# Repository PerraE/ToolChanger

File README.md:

# ToolChanger
ToolChanger for Emco 120P. 

This tool changer will be used in a PathPilot (LinuxCNC) controller for a Emoc 120P lathe
Components for PathPilot is Mesa 7i92 and 7i76,

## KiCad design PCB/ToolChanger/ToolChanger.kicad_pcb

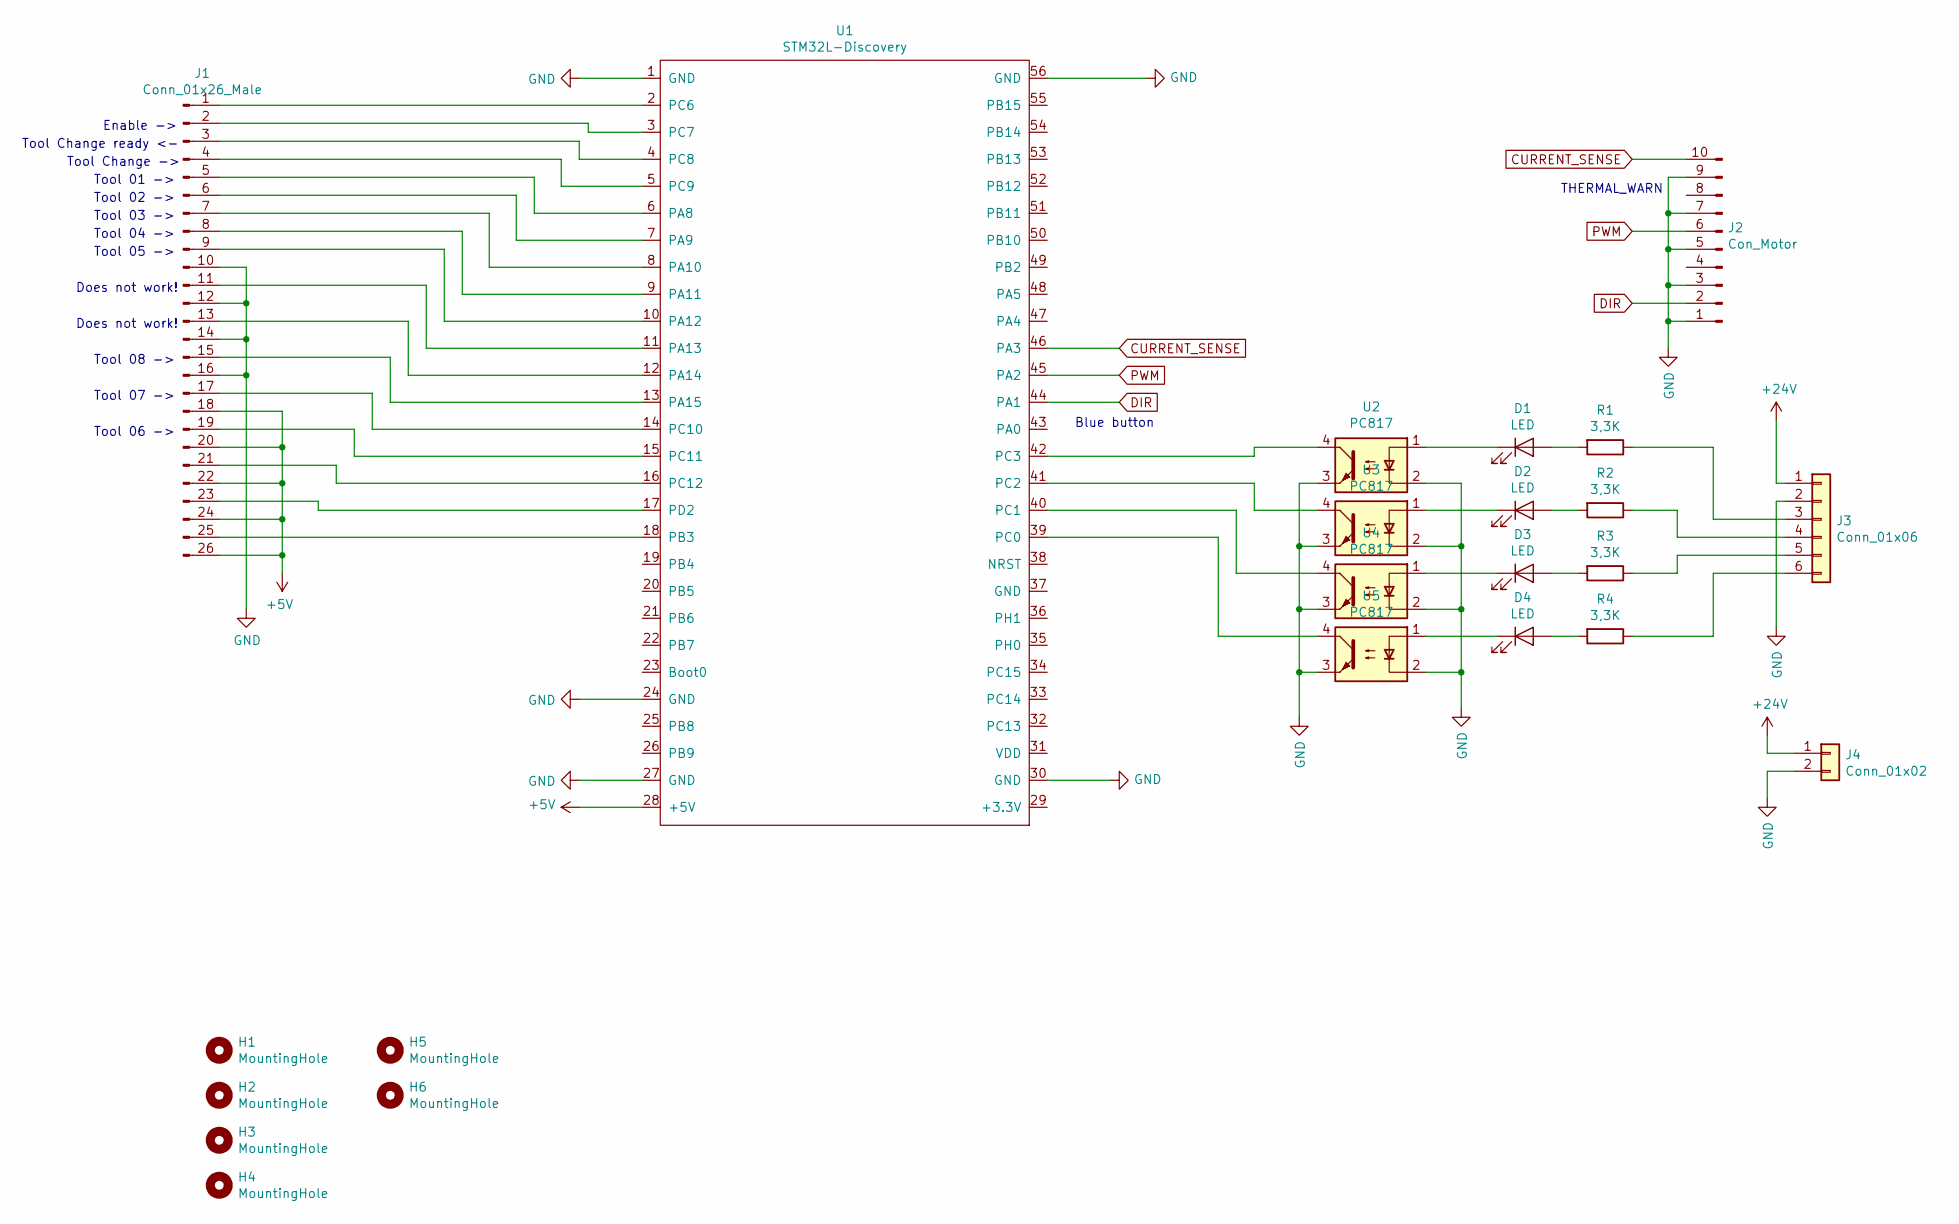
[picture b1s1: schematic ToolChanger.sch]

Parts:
D1, D2, D3, D4: LED; LED_D3.0mm
H1, H2, H3, H4, H5, H6: MountingHole; MountingHole_3.5mm
J1: Conn_01x26_Male; IDC-Header_2x13_P2.54mm_Vertical
J2: Con_Motor; IDC-Header_2x05_P2.54mm_Vertical
J3: Conn_01x06; PhoenixContact_MC_1,5_6-G-5.08_1x06_P5.08mm_Horizontal
J4: Conn_01x02; PhoenixContact_MC_1,5_2-G-5.08_1x02_P5.08mm_Horizontal
R1, R2, R3, R4: 3,3K; R_Axial_DIN0309_L9.0mm_D3.2mm_P12.70mm_Horizontal
U1: STM32L-Discovery
U2, U3, U4, U5: PC817; DIP-4_W7.62mm

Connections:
+5V: J1.18, J1.20, J1.22, J1.24, J1.26, U1.28 (+5V)
+24V: J3.1, J4.1
CURRENT_SENSE: J2.10, U1.46 (PA3)
DIR: J2.2, U1.44 (PA1)
GND: J1.10, J1.12, J1.14, J1.16, J2.1, J2.3, J2.5, J2.7, J2.9, J3.2, J4.2, U1.1 (GND), U1.24 (GND), U1.27 (GND), U1.30 (GND), U1.56 (GND), U2.2, U2.3, U3.2, U3.3, U4.2, U4.3, U5.2, U5.3
unnamed: D1.1 (K), U2.1
unnamed: D1.2 (A), R1.2
unnamed: D2.1 (K), U3.1
unnamed: D2.2 (A), R2.2
unnamed: D3.1 (K), U4.1
unnamed: D3.2 (A), R3.2
unnamed: D4.1 (K), U5.1
unnamed: D4.2 (A), R4.2
unnamed: J1.1, U1.2 (PC6)
unnamed: J1.2, U1.3 (PC7)
unnamed: J1.3, U1.4 (PC8)
unnamed: J1.4, U1.5 (PC9)
unnamed: J1.5, U1.6 (PA8)
unnamed: J1.6, U1.7 (PA9)
unnamed: J1.7, U1.8 (PA10)
unnamed: J1.8, U1.9 (PA11)
unnamed: J1.9, U1.10 (PA12)
unnamed: J1.11, U1.11 (PA13)
unnamed: J1.13, U1.12 (PA14)
unnamed: J1.15, U1.13 (PA15)
unnamed: J1.17, U1.14 (PC10)
unnamed: J1.19, U1.15 (PC11)
unnamed: J1.21, U1.16 (PC12)
unnamed: J1.23, U1.17 (PD2)
unnamed: J1.25, U1.18 (PB3)
unnamed: J3.3, R1.1
unnamed: J3.4, R2.1
unnamed: J3.5, R3.1
unnamed: J3.6, R4.1
unnamed: U1.39 (PC0), U5.4
unnamed: U1.40 (PC1), U4.4
unnamed: U1.41 (PC2), U3.4
unnamed: U1.42 (PC3), U2.4
PWM: J2.6, U1.45 (PA2)

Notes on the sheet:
Blue button
THERMAL_WARN
Enable ->
Tool Change ready <-
Tool Change ->
Tool 01 ->
Tool 02 ->
Tool 03 ->
Tool 04 ->
Tool 05 ->
Tool 06 ->
Tool 07 ->
Tool 08 ->
Does not work!

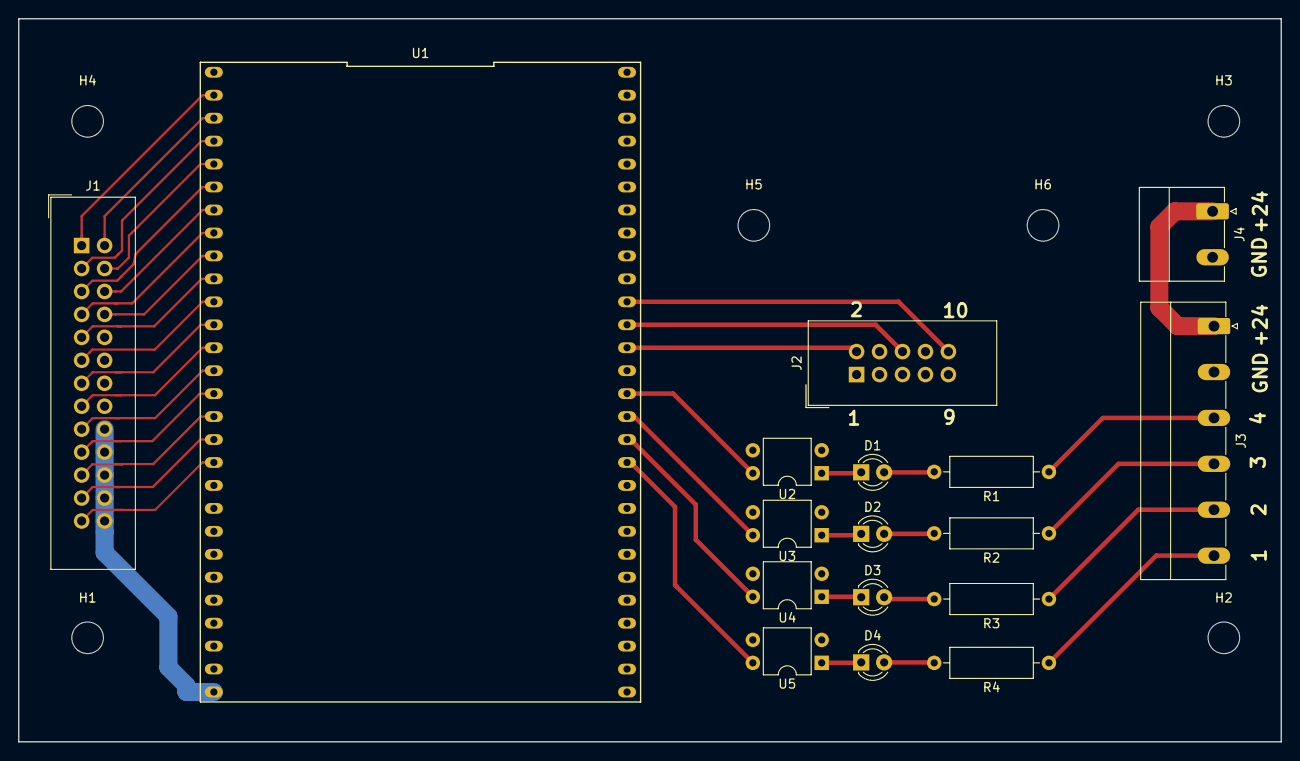
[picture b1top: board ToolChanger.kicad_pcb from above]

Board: 2 copper layers, 139.7 x 80.0 mm, 23 parts (0 on the bottom side), 39 nets.

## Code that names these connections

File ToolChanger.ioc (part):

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Mcu.Name=STM32L152R(6-8-B)Tx
Mcu.Package=LQFP64
Mcu.UserName=STM32L152RBTx
PA0-WKUP1.GPIOParameters=GPIO_Label
PA0-WKUP1.GPIO_Label=BUTTON
PA0-WKUP1.Signal=GPIO_Input
PA1.GPIOParameters=GPIO_Label
PA1.GPIO_Label=MOTOR_DIR
PA1.Signal=GPIO_Output
PA10.GPIOParameters=GPIO_Label
PA10.GPIO_Label=TOOL_SEL_3
PA10.Signal=GPIO_Input
PA11.GPIOParameters=GPIO_Label
PA11.GPIO_Label=TOOL_SEL_4
PA11.Signal=GPIO_Input
PA12.GPIOParameters=GPIO_Label
PA12.GPIO_Label=TOOL_SEL_5
PA12.Signal=GPIO_Input
PA15.GPIOParameters=GPIO_Label
PA15.GPIO_Label=TOOL_SEL_8
PA15.Signal=GPIO_Input
PA2.GPIOParameters=GPIO_Label
PA2.GPIO_Label=MOTOR_PWM
PA2.Signal=S_TIM9_CH1
PA3.GPIOParameters=GPIO_Label
PA3.GPIO_Label=MOTOR_CURENT
PA3.Signal=SharedAnalog_PA3
PA8.GPIOParameters=GPIO_Label
PA8.GPIO_Label=TOOL_SEL_1
PA8.Signal=GPIO_Input
PA9.GPIOParameters=GPIO_Label
PA9.GPIO_Label=TOOL_SEL_2
PA9.Signal=GPIO_Input
PB10.GPIOParameters=GPIO_Label
PB10.GPIO_Label=TURRET_P1
PB10.Signal=GPIO_Input
PB11.GPIOParameters=GPIO_Label
PB11.GPIO_Label=TURRET_P2
PB11.Signal=GPIO_Input
PB12.GPIOParameters=GPIO_Label
PB12.GPIO_Label=TURRET_P3
PB12.Signal=GPIO_Input
PB13.GPIOParameters=GPIO_Label
PB13.GPIO_Label=TURRET_P4
PB13.Signal=GPIO_Input
PB6.GPIOParameters=GPIO_Label
PB6.GPIO_Label=LED_LOCK
PB6.Signal=GPIO_Output
PB7.GPIOParameters=GPIO_Label
PB7.GPIO_Label=LED_ENABLED
PB7.Signal=GPIO_Output
PC0.GPIOParameters=GPIO_PuPd,GPIO_Label
PC0.GPIO_Label=ENC_1
PC0.GPIO_PuPd=GPIO_PULLUP
PC0.Signal=GPIO_Input
PC1.GPIOParameters=GPIO_PuPd,GPIO_Label
PC1.GPIO_Label=ENC_2
PC1.GPIO_PuPd=GPIO_PULLUP
PC1.Signal=GPIO_Input
PC10.GPIOParameters=GPIO_Label
PC10.GPIO_Label=TOOL_SEL_7
PC10.Signal=GPIO_Input
PC11.GPIOParameters=GPIO_Label
PC11.GPIO_Label=TOOL_SEL_6
PC11.Signal=GPIO_Input
PC2.GPIOParameters=GPIO_PuPd,GPIO_Label
PC2.GPIO_Label=ENC_3
PC2.GPIO_PuPd=GPIO_PULLUP
PC2.Signal=GPIO_Input
PC3.GPIOParameters=GPIO_PuPd,GPIO_Label
PC3.GPIO_Label=ENC_4
PC3.GPIO_PuPd=GPIO_PULLUP
PC3.Signal=GPIO_Input
PC7.GPIOParameters=GPIO_Label
PC7.GPIO_Label=ENABLE
PC7.Signal=GPIO_Input
PC8.GPIOParameters=GPIO_Label
PC8.GPIO_Label=TOOL_CHANGE_READY
PC8.Signal=GPIO_Output
PC9.GPIOParameters=GPIO_Label
PC9.GPIO_Label=TOOL_CHANGE
PC9.Signal=GPIO_Input
RCC.HSE_VALUE=24000000
RCC.SYSCLKFreq_VALUE=16000000
RCC.SYSCLKSource=RCC_SYSCLKSOURCE_HSI
board=custom

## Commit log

2020-02-08 Work commit
2020-02-11 Development progress
2020-06-26 Debuggat inkommande data för Ziox. OK
2020-07-28 Initial commit. Toolchange working
2020-08-06 Finetune
2020-08-07 Ignore Debug folder
2020-08-07 New gitignore
2020-08-22 Konvertering till STM32CubeIDE
2024-06-10 Bytt till långsammare motor
